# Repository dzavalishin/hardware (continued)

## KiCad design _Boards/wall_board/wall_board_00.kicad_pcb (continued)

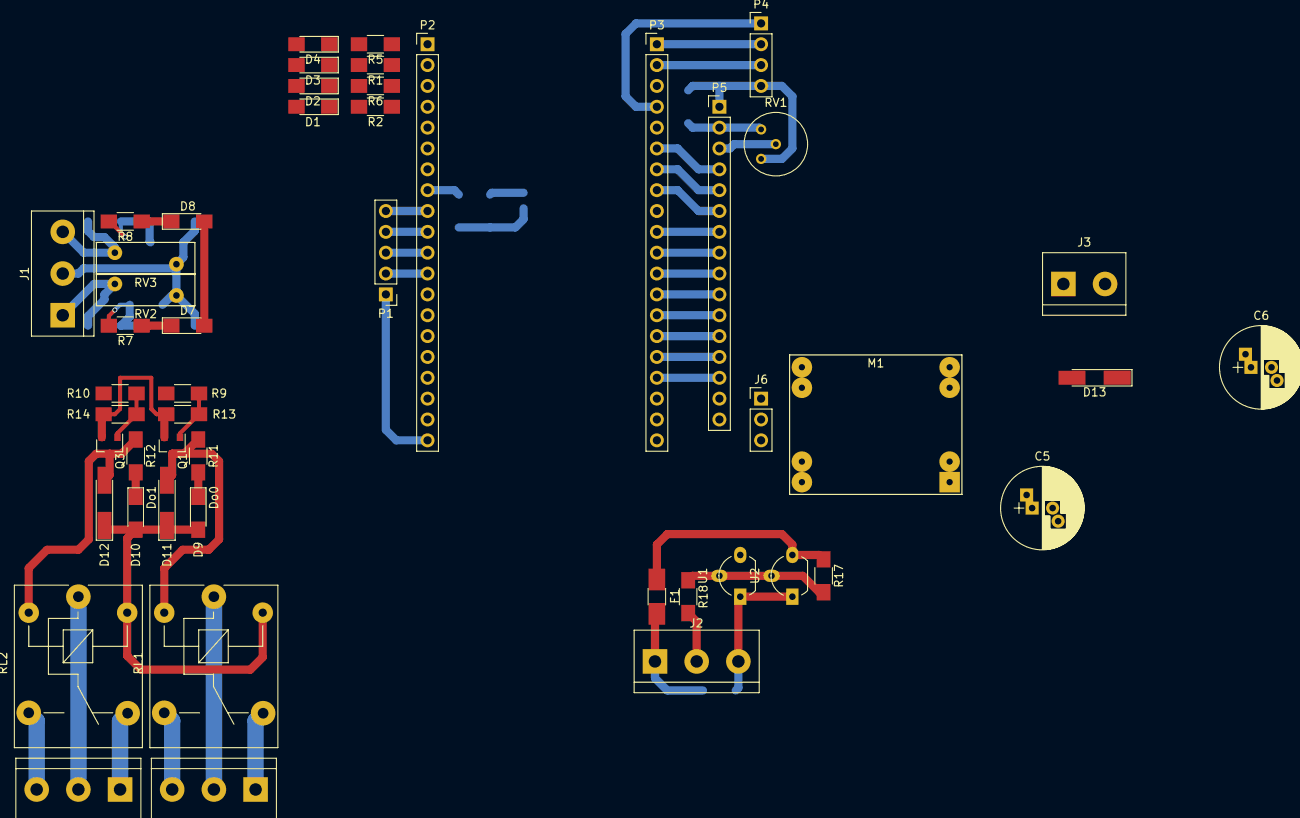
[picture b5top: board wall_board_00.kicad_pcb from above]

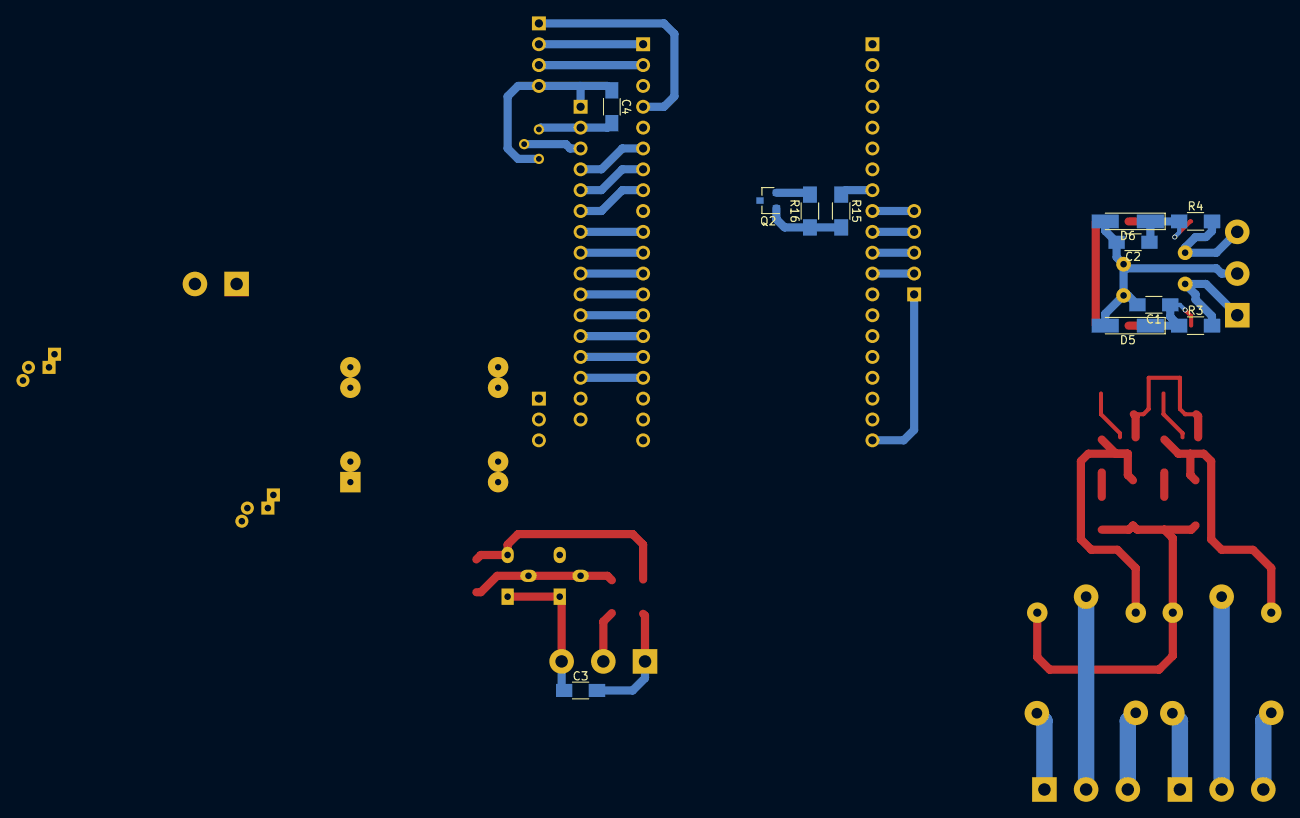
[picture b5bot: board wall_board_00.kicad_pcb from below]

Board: 2 copper layers, 60 parts (11 on the bottom side), 58 nets.

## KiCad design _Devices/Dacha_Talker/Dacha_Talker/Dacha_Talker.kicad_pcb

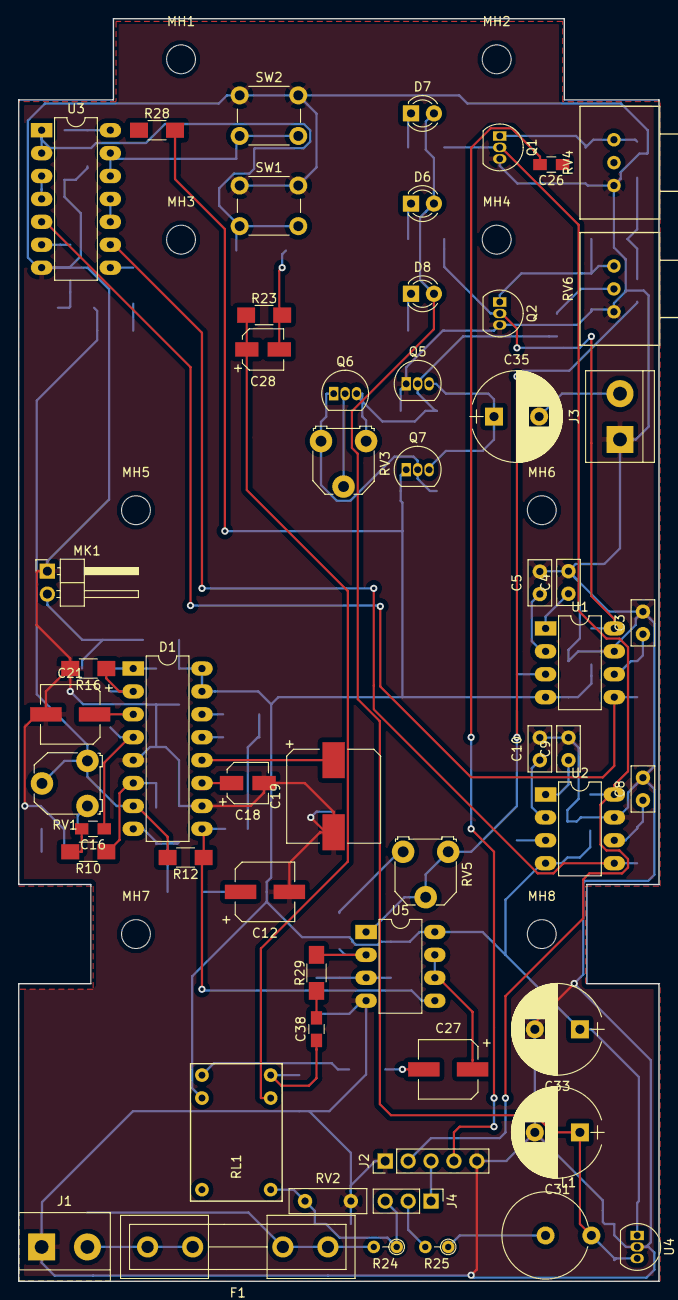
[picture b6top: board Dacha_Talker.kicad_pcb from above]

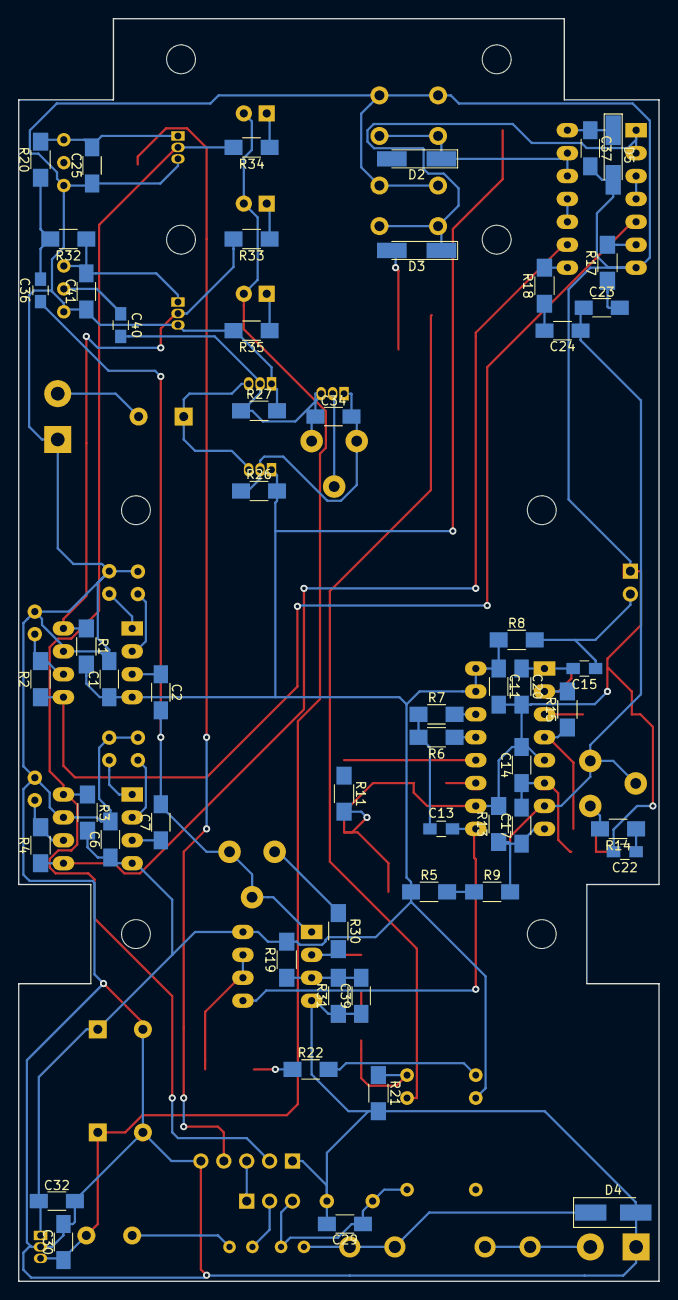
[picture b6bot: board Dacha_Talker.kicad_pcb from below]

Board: 2 copper layers, 71.0 x 140.0 mm, 118 parts (54 on the bottom side), 73 nets.

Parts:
C1, C6, C11, C37: 1,0; C_1206_HandSoldering
C2, C7, C17: 0,1; C_1206_HandSoldering
C3: 0,15; C_Disc_D5.0mm_W2.5mm_P2.50mm
C4, C9: 2.2; C_Disc_D5.0mm_W2.5mm_P2.50mm
C5: 1.0; C_Disc_D5.0mm_W2.5mm_P2.50mm
C8: 0,1; C_Disc_D5.0mm_W2.5mm_P2.50mm
C10: 0.68; C_Disc_D5.0mm_W2.5mm_P2.50mm
C12, C27: 47,0; CP_Elec_6.3x5.7
C13, C15, C16, C22, C26, C36, C38, C40: 10,0; C_0805_HandSoldering
C14: 820; C_1206_HandSoldering
C18: 4,7; CP_Elec_4x5.3
C19: 220,0; CP_Elec_10x10.5
C20: 3900; C_1206_HandSoldering
C21: 100,0; CP_Elec_6.3x5.3
C23, C24: 0,01; C_1206_HandSoldering
C25, C41: 0,022; C_1206_HandSoldering
C28: 10,0; CP_Elec_4x5.3
C29: 100pF; C_1206_HandSoldering
C30, C32, C34: 0,33; C_1206_HandSoldering
C31, C33, C35: 470,0; CP_Radial_D10.0mm_P5.00mm
C39: 10,0; C_1206_HandSoldering
D1: TDA1002A; DIP-16_W7.62mm_LongPads
D2, D3: D; D_MiniMELF_Handsoldering
D4: SS34; D_SMA_Handsoldering
D5: 5v6; D_MiniMELF_Handsoldering
D6: RxTalk; LED_D3.0mm
D7: RxLoud; LED_D3.0mm
D8: Pwr; LED_D3.0mm
F1: Fuse; Fuseholder5x20_horiz_open_inline_Type-I
J1: Line; TerminalBlock_bornier-2_P5.08mm
J2: PowerAmp; PinHeader_1x05_P2.54mm_Vertical
J3: Speaker; TerminalBlock_bornier-2_P5.08mm
J4: Power; PinHeader_1x03_P2.54mm_Vertical
L1: 220mH; L_Axial_L16.0mm_D9.5mm_P5.08mm_Vertical_Vishay_IM-10-37
MH1, MH2, MH3, MH4, MH5, MH6, MH7, MH8: -; MountingHole_3.2mm_M3
MK1: Microphone_Condenser; Pin_Header_Angled_1x02_Pitch2.54mm
Q1, Q2: BS107; TO-92_Inline
Q5: BC557; TO-92_Inline
Q6, Q7: BC547; TO-92_Inline
R1, R3, R6, R7, R19, R20, R31, R32: 10k; R_1206_HandSoldering
R2, R4: 2,4k; R_1206_HandSoldering
R5, R10: 33k; R_1206_HandSoldering
R8, R15: 22k; R_1206_HandSoldering
R9: 68k; R_1206_HandSoldering
R11: 1M; R_1206_HandSoldering
R12: 56k; R_1206_HandSoldering
R13, R29, R30: 100k; R_1206_HandSoldering
R14: 56; R_1206_HandSoldering
R16: 220; R_1206_HandSoldering
R17, R18: 150k; R_1206_HandSoldering
R21: 1m; R_1206_HandSoldering
R22, R23: 100; R_1206_HandSoldering
R24: 2; R_Axial_DIN0204_L3.6mm_D1.6mm_P2.54mm_Vertical
R25: 10; R_Axial_DIN0204_L3.6mm_D1.6mm_P2.54mm_Vertical
R26, R27, R28, R33, R34, R35: 1k; R_1206_HandSoldering
RL1: HK4100F; Relay_SPDT_HK4100F
RV1, RV3: 560; Potentiometer_Triwood_RM-065
RV2: 36v; R_Box_L8.4mm_W2.5mm_P5.08mm
RV4, RV6: 100k; Potentiometer_Spectrol-Type148-Type149_Single
RV5: 200k; Potentiometer_Triwood_RM-065
SW1: Talk; SW_PUSH_6mm_h13mm
SW2: Loud; SW_PUSH_6mm_h13mm
U1, U2: NE567; DIP-8_W7.62mm_LongPads
U3: 74HC00; DIP-14_W7.62mm_LongPads
U4: L78L09_TO92; TO-92_Inline
U5: LM2904; DIP-8_W7.62mm_LongPads

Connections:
+9V: C1.1, C6.1, C11.1, C32.1, C33.1, D1.15, D1.16, Q7.1, R1.2, R3.2, R5.1, R8.1, R19.2, R26.2, R28.2, RL1.5, U1.4, U2.4, U4.1, U5.8
+12P: J2.3, J4.1
+12V: C30.1, C31.1, D6.2, D7.2, D8.2, L1.2, U4.3
/Amp: C41.2, Q2.1, R32.1, RV6.3
/Coil: C28.2, D2.2, D3.2, R23.2
/F1: R2.1, U1.5, U3.5
/F2: R4.1, U2.5, U3.9
/FromLine: C38.1, R21.1, RL1.3
/Fx: C2.2, C7.2, C36.1, RV5.1, RV5.2, U5.1
/MicOut: C13.2, D1.9, R12.1, U5.5
/~Enable_A: Q2.2, R1.1, R33.2, U1.8
/~Enable_B: J2.2, Q1.2, R3.1, R34.2, U2.8
GND: C1.2, C3.2, C4.2, C5.2, C6.2, C8.2, C9.2, C10.2, C11.2, C12.2, C14.2, C18.2, C19.2, C20.2, C21.2, C22.2, C25.1, C29.2, C30.2, C31.2, C32.2, C33.2, C37.2, C39.1, C41.1, D1.5, D1.10, D4.2, D5.2, J1.1, J2.1, J2.5, J3.1, MK1.1, Q1.3, Q2.3, Q5.1, R11.2, R13.2, R16.2, R21.2, R27.2, R31.1, R35.2, RV2.2, RV4.1, RV6.1, SW1.1, SW2.1, U1.7, U2.7, U3.7, U4.2, U5.4
unnamed: C2.1, U1.3
unnamed: C3.1, R2.2, U1.6
unnamed: C4.1, U1.1
unnamed: C5.1, U1.2
unnamed: C7.1, U2.3
unnamed: C8.1, R4.2, U2.6
unnamed: C9.1, U2.1
unnamed: C10.1, U2.2
unnamed: C12.1, R5.2, R9.1
unnamed: C13.1, R6.2, R7.1
unnamed: C14.1, C17.2, D1.6, R10.1
unnamed: C15.1, MK1.2, R8.2
unnamed: C15.2, C20.1, D1.1
unnamed: C16.1, D1.4, R15.1
unnamed: C16.2, R10.2
unnamed: C17.1, D1.8, R9.2, R13.1
unnamed: C18.1, D1.11
unnamed: C19.1, D1.12, R11.1
unnamed: C21.1, D1.3
unnamed: C22.1, R14.1
unnamed: C23.1, C24.1, D1.7, R12.2, RV1.2, RV1.3
unnamed: C23.2, R17.1
unnamed: C24.2, R18.1
unnamed: C25.2, Q1.1, R20.2, RV4.3
unnamed: C26.1, RV4.2
unnamed: C26.2, J2.4
unnamed: C27.1, U5.6, U5.7
unnamed: C27.2, R22.1
unnamed: C28.1, R23.1, RL1.2
unnamed: C29.1, J4.3, R24.1, RL1.1, RV2.1
unnamed: C34.1, C40.2, Q5.2, Q6.3, R27.1, RV3.1
unnamed: C34.2, Q6.1, Q7.2, R26.1, RV3.3
unnamed: C35.1, Q5.3, Q7.3
unnamed: C35.2, J3.2
unnamed: C36.2, R20.1, R32.2
unnamed: C37.1, D5.1, R28.1, U3.14
unnamed: C38.2, R29.1
unnamed: C39.2, R19.1, R31.2, U5.3
unnamed: C40.1, RV6.2
unnamed: D1.2, R15.2, R16.1
unnamed: D1.13, R6.1
unnamed: D1.14, R7.2
unnamed: D2.1, SW2.2, U3.12, U3.13
unnamed: D3.1, SW1.2, U3.1, U3.2
unnamed: D4.1, F1.1, R24.2
unnamed: D6.1, R33.1
unnamed: D7.1, R34.1
unnamed: D8.1, R35.1
unnamed: F1.2, J1.2
unnamed: J4.2, R25.2
unnamed: L1.1, R25.1
unnamed: Q6.2, RV3.2
unnamed: R14.2, RV1.1
unnamed: R17.2, U3.6
unnamed: R18.2, U3.8
unnamed: R22.2, RL1.4
unnamed: R29.2, R30.2, U5.2
unnamed: R30.1, RV5.3
unnamed: U3.3, U3.4
unnamed: U3.10, U3.11

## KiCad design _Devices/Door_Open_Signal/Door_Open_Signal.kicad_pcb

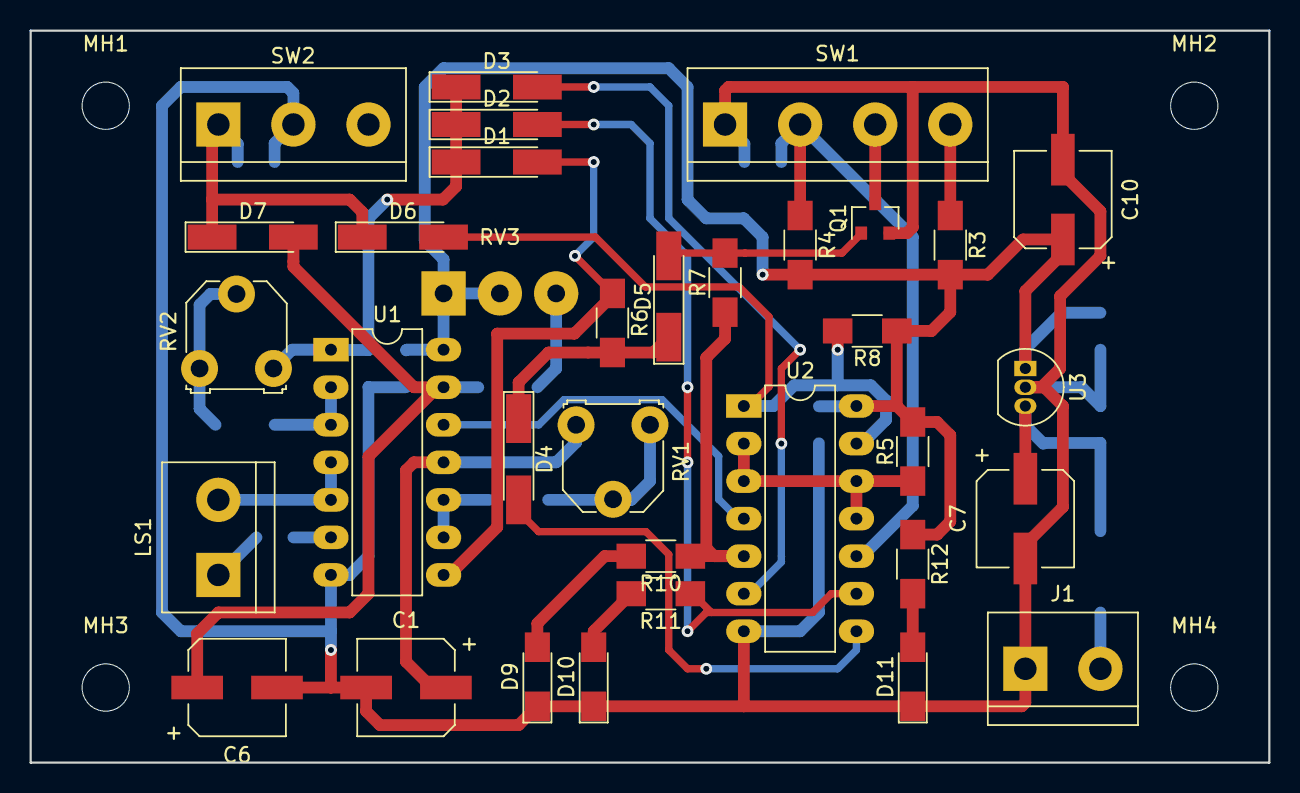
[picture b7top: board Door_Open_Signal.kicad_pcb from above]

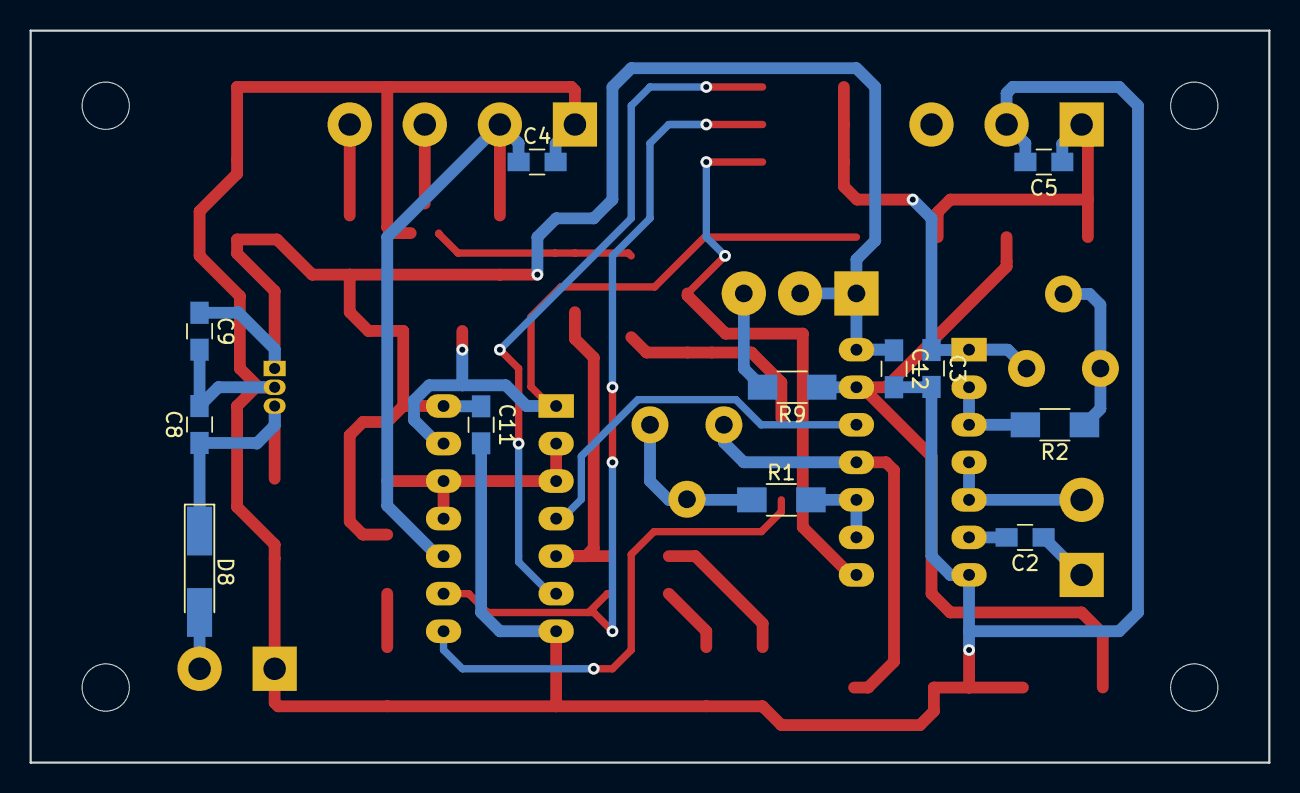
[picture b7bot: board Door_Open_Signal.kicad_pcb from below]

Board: 2 copper layers, 83.8 x 49.5 mm, 50 parts (12 on the bottom side), 32 nets.

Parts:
C1: 22,0; CP_Elec_6.3x5.3
C2: 1,0; C_0805_HandSoldering
C3, C4, C11, C12: 0,1; C_0805_HandSoldering
C5: 0,01; C_0805_HandSoldering
C6, C7: 100,0; CP_Elec_6.3x5.3
C8, C9: 0,33; C_0805_HandSoldering
C10: 47,0; CP_Elec_6.3x5.3
D1, D2, D3, D4, D5, D6, D7, D8: 4148; D_MiniMELF_Handsoldering
D9: Sig; LED_1206_HandSoldering
D10: Dis; LED_1206_HandSoldering
D11: Pwr; LED_1206_HandSoldering
J1: +12; TerminalBlock_bornier-2_P5.08mm
LS1: Speaker_Crystal; TerminalBlock_bornier-2_P5.08mm
MH1, MH2, MH3, MH4: -; MountingHole_3.2mm_M3
Q1: MMBT3904; SOT-23
R1, R2: 5,6k; R_1206_HandSoldering
R3: 560; R_1206_HandSoldering
R4, R5, R6, R10, R11, R12: 1k; R_1206_HandSoldering
R7: 10k; R_1206_HandSoldering
R8: 100k; R_1206_HandSoldering
R9: 56k; R_1206_HandSoldering
RV1: 20k; Potentiometer_Triwood_RM-065
RV2: 4,7k; Potentiometer_Triwood_RM-065
RV3: 100k; SolderWirePad_1x03_P3.81mm_Drill1.2mm
SW1: Disable; TerminalBlock_bornier-4_P5.08mm
SW2: DoorOpen; TerminalBlock_bornier-3_P5.08mm
U1: 74HC14; DIP-14_W7.62mm_LongPads
U2: 74HC74; DIP-14_W7.62mm_LongPads
U3: L78L05_TO92; TO-92_Inline

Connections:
+5V: C9.1, C10.1, C11.1, C12.1, R3.2, R4.2, R5.2, R8.1, R12.1, RV3.1, RV3.2, U1.14, U2.14, U3.1
/Clock: D1.2, R6.1, U1.8
/Disabled: D2.2, R11.1, U2.9
/Signal: R7.1, R10.1, U2.5
/~Disabled: D4.2, U2.8
/~DoorClosed: D6.2, R8.2, U2.1, U2.13
/~DoorOpen: U1.12, U2.4
/~Signal: D3.2, U2.6
GND: C1.2, C3.2, C4.2, C5.2, C6.2, C7.2, C8.2, C9.2, C10.2, C11.2, C12.2, D9.1, D10.1, D11.1, J1.1, Q1.2, SW1.1, SW2.2, U1.7, U2.7, U3.2
unnamed: C1.1, RV1.3, U1.11
unnamed: C2.1, LS1.1
unnamed: C2.2, U1.6
unnamed: C3.1, D1.1, D2.1, D3.1, RV2.3, U1.1
unnamed: C4.1, R4.1, SW1.2, U2.10
unnamed: C5.1, D6.1, D7.1, SW2.1
unnamed: C6.1, D7.2, R9.1, U1.13
unnamed: C7.1, C8.1, D8.1, U3.3
unnamed: D4.1, D5.1, R6.2
unnamed: D5.2, Q1.1, R7.2
unnamed: D8.2, J1.2
unnamed: D9.2, R10.2
unnamed: D10.2, R11.2
unnamed: D11.2, R12.2
unnamed: LS1.2, U1.4, U1.5
unnamed: Q1.3, SW1.3
unnamed: R1.1, RV1.1, RV1.2
unnamed: R1.2, U1.9, U1.10
unnamed: R2.1, RV2.1, RV2.2
unnamed: R2.2, U1.2, U1.3
unnamed: R3.1, SW1.4
unnamed: R5.1, U2.2, U2.3, U2.11, U2.12
unnamed: R9.2, RV3.3
